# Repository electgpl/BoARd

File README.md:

# Board

Placa de desarrollo basada en Microchip de bajo costo, proyecto realizado de manera simple para poder ser replicado por alumnos de escuelas sin la necesidad de importar componentes y con la facilidad de realizar el circuito impreso por ellos mismos en una sola capa

  - [picc] PIC16F883 con Bootloader (Carga de fuente y Terminal Serie)
  - PCB Simple en 1 Layer realizado con Eagle
  - Bootloader oficial Micochip (AN1310) 9600bps
  - Multiples IDEs y lenguajes

Se ha probado con diversos IDEs y Lenguajes con resultados satisfactorios

> [picc] - PCWHD (PICC)
> [mplabx] - MPALB X
> [mikroc] - MikroC
> [ldmicro] - LDmicro
> [eagle] - Eagle

## Lenguajes

* Assembly
* C
* C++
* Basic
* Visual
* Ladder
* Scratch

### Instalacion (Windows)

Se debe descargar el acrhivo zip de la nota AN1310, donde encontraremos el programa ejecutable de Windows.
[AN1310]

License
----

MIT

**Free Software, Hell Yeah!**

   [picc]: <http://www.ccsinfo.com/>
   [mplabx]: <http://www.microchip.com/mplab/mplab-x-ide>
   [eagle]: <https://www.autodesk.com/education/free-software/eagle>
   [mikroc]: <https://www.mikroe.com/mikroc/>
   [ldmicro]: <http://cq.cx/ladder.pl>
   [AN1310]: <http://www.microchip.com/wwwAppNotes/AppNotes.aspx?appnote=en546974>

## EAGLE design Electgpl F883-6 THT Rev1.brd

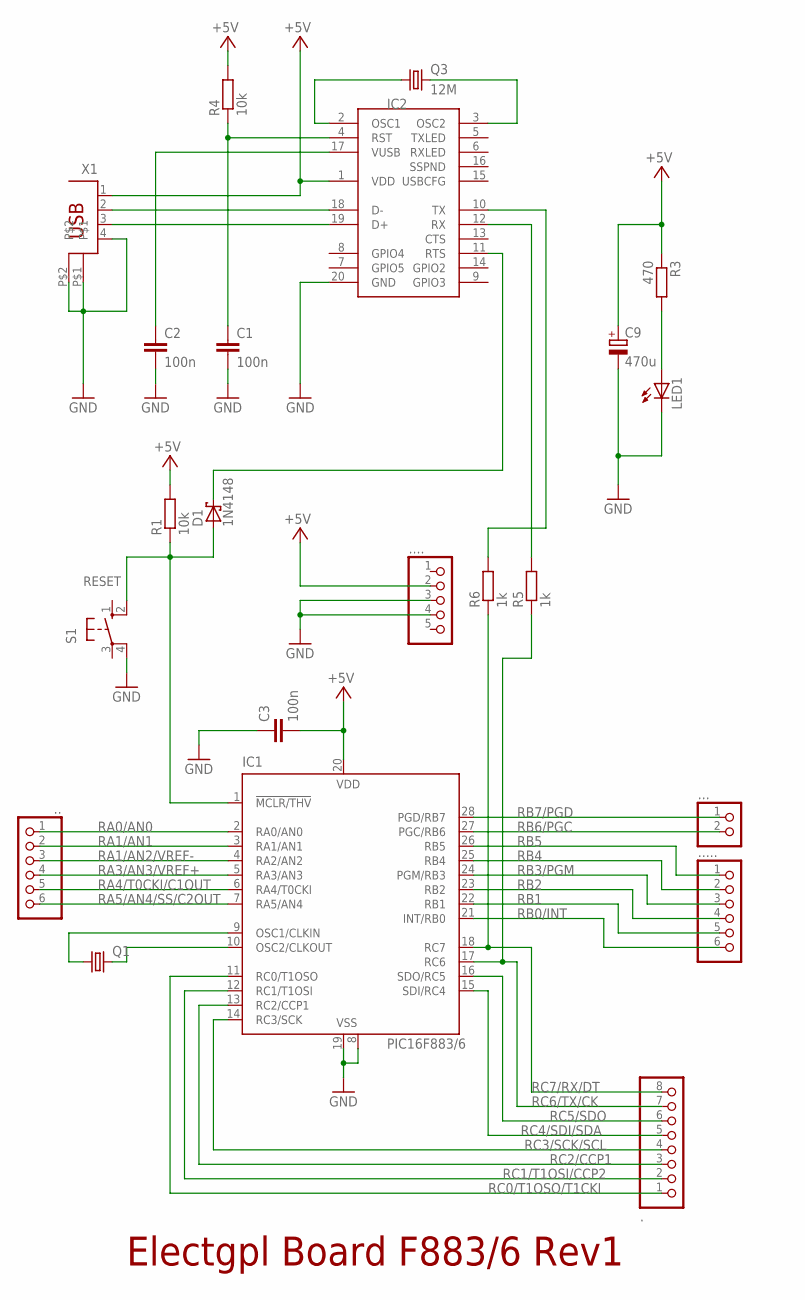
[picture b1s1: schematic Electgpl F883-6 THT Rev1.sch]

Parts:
.: PINHD-1X8; 1X08
.., .....: PINHD-1X6; 1X06
...: PINHD-1X2; 1X02
....: PINHD-1X5; 1X05
C1, C2, C3: 100n; C025-024X044
C9: 470u; E3,5-10
D1: 1N4148; DO35-7
IC1: PIC16F883/6; DIL28-3
IC2: MCP2200SOIC20; SOIC20
LED1: LED3MM
Q1: CRYSTALHC49S; HC49/S
Q3: 12M; HC49/S
R1, R4: 10k; 0204/5
R3: 470; 0204/5
R5, R6: 1k; 0204/5
S1: 10-XX; B3F-10XX
X1: PN61729

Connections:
+5V: .....2, C3.2, C9.+, IC1.20 (VDD), IC2.1 (VDD), R1.2, R3.1, R4.2, X1.1
GND: .....3, .....4, C1.2, C2.2, C3.1, C9.-, IC1.8 (VSS), IC1.19 (VSS), IC2.20 (GND), LED1.K (C), S1.4 (P1), X1.4, X1.P$1, X1.P$2
unnamed: IC1.10 (OSC2/CLKOUT), Q1.2
unnamed: IC1.9 (OSC1/CLKIN), Q1.1
unnamed: LED1.A, R3.2
unnamed: D1.C, IC2.11 (RTS)
unnamed: IC2.18 (D-), X1.2
unnamed: IC2.12 (RX), R5.2
unnamed: IC2.10 (TX), R6.2
unnamed: IC2.19 (D+), X1.3
unnamed: C1.1, IC2.4 (RST), R4.1
unnamed: IC2.2 (OSC1), Q3.1
unnamed: IC2.3 (OSC2), Q3.2
unnamed: C2.1, IC2.17 (VUSB)
RA0/AN0: ...1, IC1.2 (RA0/AN0)
RA1/AN1: ...2, IC1.3 (RA1/AN1)
RA1/AN2/VREF-: ...3, IC1.4 (RA2/AN2)
RA3/AN3/VREF+: ...4, IC1.5 (RA3/AN3)
RA4/T0CKI/C1OUT: ...5, IC1.6 (RA4/T0CKI)
RA5/AN4/SS/C2OUT: ...6, IC1.7 (RA5/AN4)
RB0/INT: ......6, IC1.21 (INT/RB0)
RB1: ......5, IC1.22 (RB1)
RB2: ......4, IC1.23 (RB2)
RB3/PGM: ......3, IC1.24 (PGM/RB3)
RB4: ......2, IC1.25 (RB4)
RB5: ......1, IC1.26 (RB5)
RB6/PGC: ....2, IC1.27 (PGC/RB6)
RB7/PGD: ....1, IC1.28 (PGD/RB7)
RC0/T1OSO/T1CKI: ..1, IC1.11 (RC0/T1OSO)
RC1/T1OSI/CCP2: ..2, IC1.12 (RC1/T1OSI)
RC2/CCP1: ..3, IC1.13 (RC2/CCP1)
RC3/SCK/SCL: ..4, IC1.14 (RC3/SCK)
RC4/SDI/SDA: ..5, IC1.15 (SDI/RC4)
RC5/SDO: ..6, IC1.16 (SDO/RC5)
RC6/TX/CK: ..7, IC1.17 (RC6), R5.1
RC7/RX/DT: ..8, IC1.18 (RC7), R6.1
RESET: D1.A, IC1.1 (!MCLR/THV), R1.1, S1.2 (S1)

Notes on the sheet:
Electgpl Board F883/6 Rev1

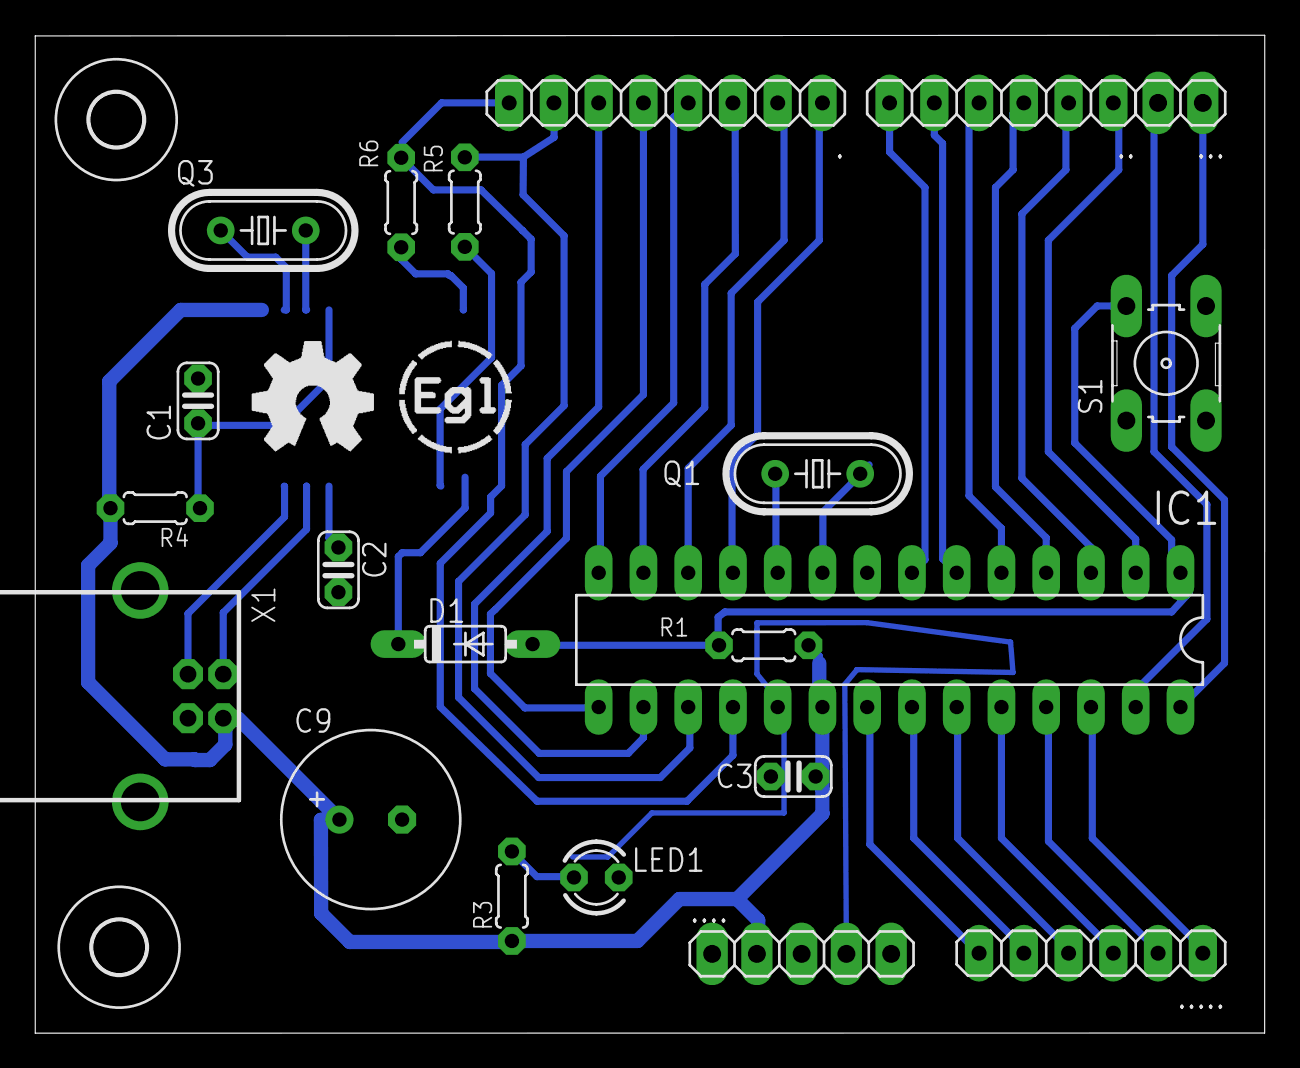
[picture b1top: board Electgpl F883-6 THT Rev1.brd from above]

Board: 2 copper layers, 69.8 x 56.6 mm, 24 parts (1 on the bottom side), 37 nets.

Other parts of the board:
U$2, U$3: 3,0
